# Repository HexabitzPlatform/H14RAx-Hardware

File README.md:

# H14RAx-Hardware
Hexabitz 6 x 5V PWM O/P Module Hardware Design

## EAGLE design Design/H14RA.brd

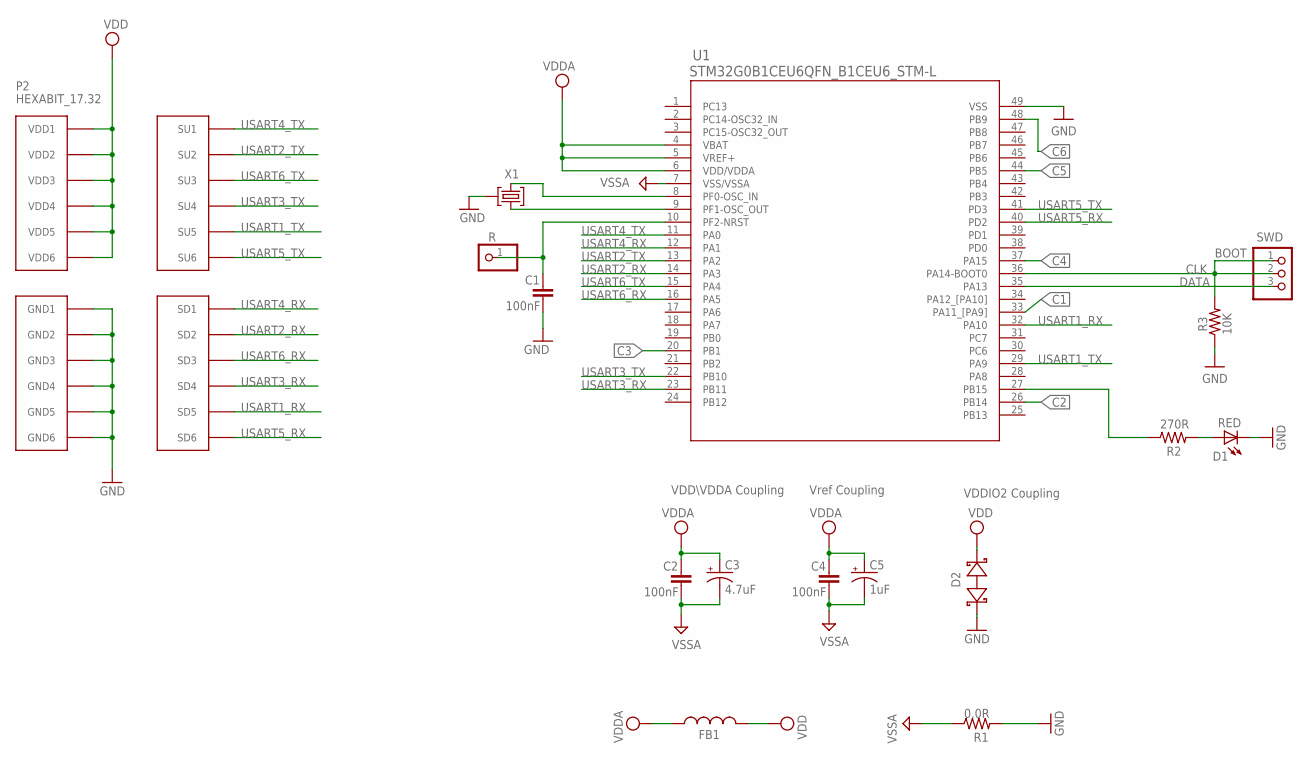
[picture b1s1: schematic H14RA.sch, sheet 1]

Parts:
C1, C2, C4: 100nF; C-0603
C3: 4.7uF; C-0805-POL
C5: 1uF; C-0805-POL
D1: RED; VLMS1300-GS08; MPN VLMS1300-GS08
D2: BOURNS_CDSOD323-T03SCBOURNS_CDSOD323-T03SC_0_0; BOURNS_CDSOD323-T03SC_0
FB1: FB-0603
P2: HEXABIT_17.32
R: R; 1X01
R1: 0.0R; R-0603
R2: 270R; R-0603
R3: 10K; R-0603
SWD: PINHD-1X3; 1X03
TRIMBLE-LOGO2: HEXA-LOGO
U1: STM32G0B1CEU6QFN_B1CEU6_STM-L; QFN_B1CEU6_STM-L
X1: XTALL_CSTCE8M00G52

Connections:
C1: U1.33 (PA11_[PA9]); also elsewhere on the board
C2: U1.26 (PB14); also elsewhere on the board
C3: U1.20 (PB1); also elsewhere on the board
C4: U1.37 (PA15); also elsewhere on the board
C5: U1.44 (PB5); also elsewhere on the board
C6: U1.48 (PB9); also elsewhere on the board
CLK: R3.2, SWD.1, SWD.2, U1.36 (PA14-BOOT0)
DATA: SWD.3, U1.35 (PA13)
GND: C1.2, D1.C, D2.1 (A), P2.PAD_PD7 (GND1), P2.PAD_PD8 (GND2), P2.PAD_PD9 (GND3), P2.PAD_PD10 (GND4), P2.PAD_PD11 (GND5), P2.PAD_PD12 (GND6), R1.2, R3.1, U1.49 (VSS), X1.P$2 (2)
unnamed: D1.A, R2.2
unnamed: R2.1, U1.27 (PB15)
unnamed: U1.9 (PF1-OSC_OUT), X1.P$1 (1)
unnamed: U1.8 (PF0-OSC_IN), X1.P$3 (3)
unnamed: C1.1, R.1, U1.10 (PF2-NRST)
USART1_RX: P2.PAD_PD5 (SD5), U1.32 (PA10)
USART1_TX: P2.PAD_PU5 (SU5), U1.29 (PA9)
USART2_RX: P2.PAD_PD2 (SD2), U1.14 (PA3)
USART2_TX: P2.PAD_PU2 (SU2), U1.13 (PA2)
USART3_RX: P2.PAD_PD4 (SD4), U1.23 (PB11)
USART3_TX: P2.PAD_PU4 (SU4), U1.22 (PB10)
USART4_RX: P2.PAD_PD1 (SD1), U1.12 (PA1)
USART4_TX: P2.PAD_PU1 (SU1), U1.11 (PA0)
USART5_RX: P2.PAD_PD6 (SD6), U1.40 (PD2)
USART5_TX: P2.PAD_PU6 (SU6), U1.41 (PD3)
USART6_RX: P2.PAD_PD3 (SD3), U1.16 (PA5)
USART6_TX: P2.PAD_PU3 (SU3), U1.15 (PA4)
VDD: D2.2 (C), FB1.2, P2.PAD_PU7 (VDD1), P2.PAD_PU8 (VDD2), P2.PAD_PU9 (VDD3), P2.PAD_PU10 (VDD4), P2.PAD_PU11 (VDD5), P2.PAD_PU12 (VDD6)
VDDA: C2.1, C3.1 (+), C4.1, C5.1 (+), FB1.1, U1.4 (VBAT), U1.5 (VREF+), U1.6 (VDD/VDDA); also elsewhere on the board
VSSA: C2.2, C3.2 (-), C4.2, C5.2 (-), R1.1, U1.7 (VSS/VSSA); also elsewhere on the board

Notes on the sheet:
Vref Coupling
VDDIO2 Coupling
VDD\VDDA Coupling
BOOT

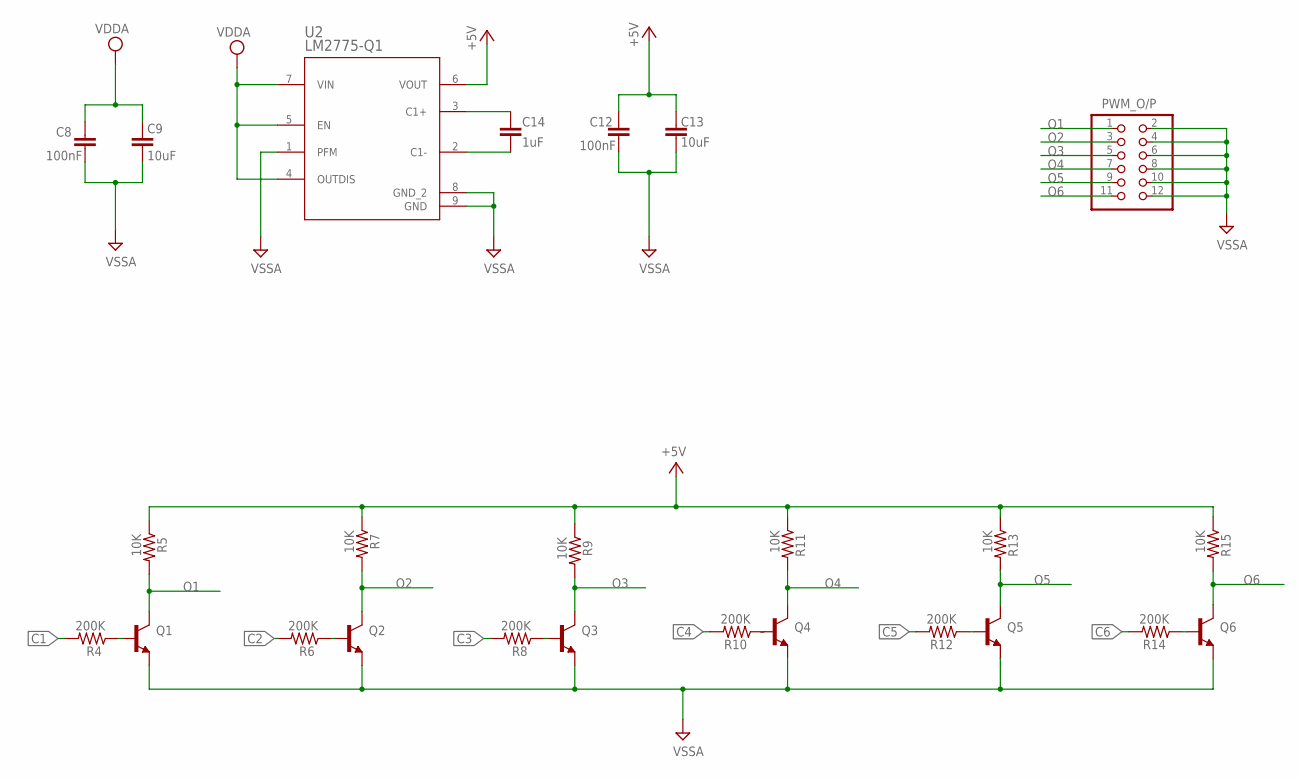
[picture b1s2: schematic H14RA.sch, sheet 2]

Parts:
C8, C12: 100nF; C-0603
C9, C13: 10uF; C-0603
C14: 1uF; C-0805
PWM_O/P: PINHD-2X6; 2X06
Q1, Q2, Q3, Q4, Q5, Q6: MMBT3904LT1
R4, R6, R8, R10, R12, R14: 200K; R-0603
R5, R7, R9, R11, R13, R15: 10K; R-0603
U2: LM2775-Q1; DSG0008A

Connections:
+5V: C12.1, C13.1, R5.1, R7.1, R9.1, R11.1, R13.1, R15.1, U2.6 (VOUT)
C1: R4.2; also elsewhere on the board
C2: R6.2; also elsewhere on the board
C3: R8.2; also elsewhere on the board
C4: R10.2; also elsewhere on the board
C5: R12.2; also elsewhere on the board
C6: R14.2; also elsewhere on the board
unnamed: C14.2, U2.2 (C1-)
unnamed: C14.1, U2.3 (C1+)
unnamed: Q5.1 (B), R12.1
unnamed: Q4.1 (B), R10.1
unnamed: Q6.1 (B), R14.1
unnamed: Q2.1 (B), R6.1
unnamed: Q1.1 (B), R4.1
unnamed: Q3.1 (B), R8.1
O1: PWM_O/P.1, Q1.3 (C), R5.2
O2: PWM_O/P.3, Q2.3 (C), R7.2
O3: PWM_O/P.5, Q3.3 (C), R9.2
O4: PWM_O/P.7, Q4.3 (C), R11.2
O5: PWM_O/P.9, Q5.3 (C), R13.2
O6: PWM_O/P.11, Q6.3 (C), R15.2
VDDA: C8.1, C9.1, U2.4 (OUTDIS), U2.5 (EN), U2.7 (VIN); also elsewhere on the board
VSSA: C8.2, C9.2, C12.2, C13.2, PWM_O/P.2, PWM_O/P.4, PWM_O/P.6, PWM_O/P.8, PWM_O/P.10, PWM_O/P.12, Q1.2 (E), Q2.2 (E), Q3.2 (E), Q4.2 (E), Q5.2 (E), Q6.2 (E), U2.1 (PFM), U2.8 (GND_2), U2.9 (GND); also elsewhere on the board

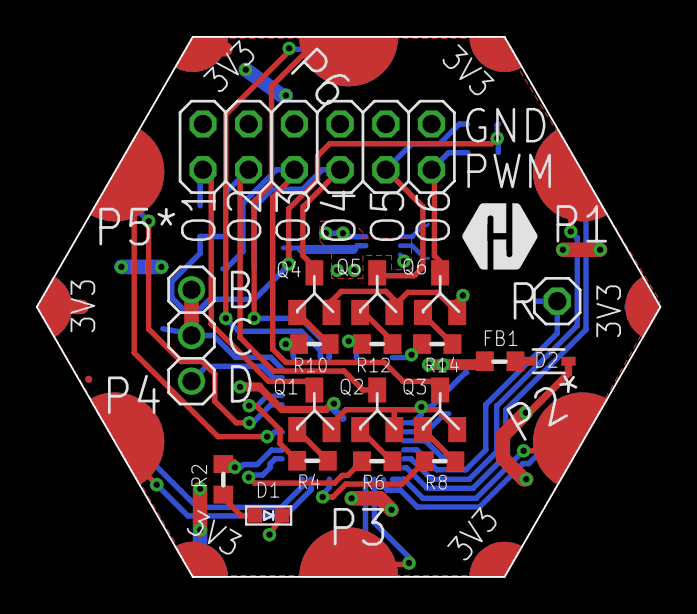
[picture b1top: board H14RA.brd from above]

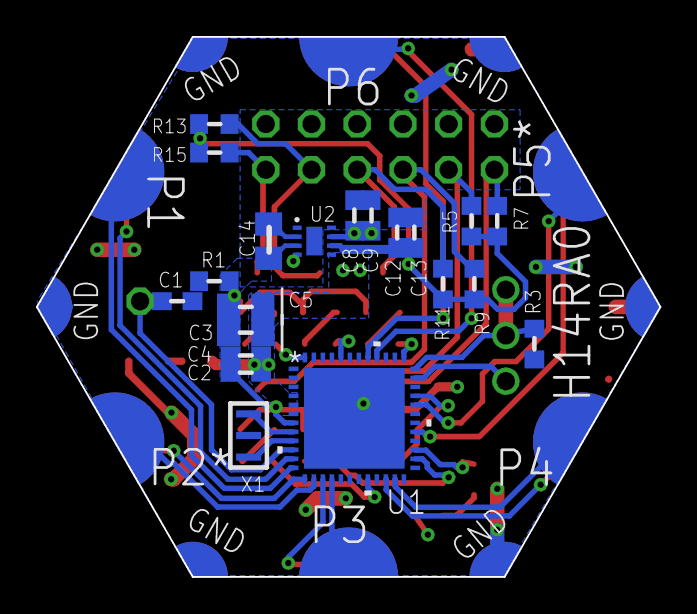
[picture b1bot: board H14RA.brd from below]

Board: 2 copper layers, 34.6 x 30.0 mm, 42 parts (21 on the bottom side), 44 nets.

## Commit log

2023-09-16 -First Version
2023-11-16 -Correcting some documentaion isses
2024-12-26 -Fix the issue with an MCU pin that cannot output PWM signals. -Update the design and BOM to reflect the latest modifications in the Platform Hardware rules.

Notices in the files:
parts and their libraries:
COPYRIGHT: Copyright (C) 2021 Ultra Librarian. All rights reserved.
